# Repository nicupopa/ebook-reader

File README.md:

# OpenBook

## Block Diagram:

## Bill of Materials:

|Component    |Footprint                                    |Link                                                                                                        |
|-------------|---------------------------------------------|------------------------------------------------------------------------------------------------------------|
|BOOT_BUTTON  |BUTTON_CUSYOMV1                              |https://industry.panasonic.com/global/en/products/control/switch/light-touch/number/evqpuj02k               |
|C1           |ESP32_WROVER_EAGLE-LTSPICE_CC0402            |https://eu.mouser.com/ProductDetail/YAGEO/CC0402MRX5R5BB106?qs=zEY9bCHj09eCmUJdZuS5Lg%3D%3D                 |
|C1_BAT       |ESP32_WROVER_EAGLE-LTSPICE_CC0402            |n/a                                                                                                         |
|C1_BAT1      |EAGLE-LTSPICE_CC0402                         |n/a                                                                                                         |
|C1_BAT2      |EAGLE-LTSPICE_CC0402                         |n/a                                                                                                         |
|C2           |ESP32_WROVER_EAGLE-LTSPICE_CC0402            |n/a                                                                                                         |
|C2_BAT\      |ESP32_WROVER_EAGLE-LTSPICE_CC0402            |n/a                                                                                                         |
|C3           |RCL_CPOL-EUCT3528                            |n/a                                                                                                         |
|C4           |ESP32_WROVER_EAGLE-LTSPICE_CC0402            |n/a                                                                                                         |
|C4_USB       |ESP32_WROVER_EAGLE-LTSPICE_CC0402            |n/a                                                                                                         |
|C5           |ESP32_WROVER_EAGLE-LTSPICE_CC0402            |n/a                                                                                                         |
|C5_USB       |ESP32_WROVER_EAGLE-LTSPICE_CC0402            |n/a                                                                                                         |
|C6           |ESP32_WROVER_EAGLE-LTSPICE_CC0402            |n/a                                                                                                         |
|C7           |ESP32_WROVER_EAGLE-LTSPICE_CC0402            |n/a                                                                                                         |
|C8           |ESP32_WROVER_EAGLE-LTSPICE_CC0402            |n/a                                                                                                         |
|C9           |EAGLE-LTSPICE_CC0402                         |n/a                                                                                                         |
|C10          |ESP32_WROVER_EAGLE-LTSPICE_CC0402            |n/a                                                                                                         |
|C10_SUPERCAP |CPH3225A                                     |https://www.snapeda.com/parts/CPH3225A/Seiko+Instruments/view-part/?ref=eda                                 |
|CHANGE_BUTTON|BUTTON_CUSYOMV1                              |https://industry.panasonic.com/global/en/products/control/switch-light-touch/number/evqpuj02k               |
|CHG_LED      |ADAFRUIT_LEDCHIP-LED0603                     |https://www.snapeda.com/parts/KP-1608SURCK/Kingbright/view-part/?ref=search&t=LED%200603                    |
|C_DELAY      |ESP32_WROVER_EAGLE-LTSPICE_CC0402            |n/a                                                                                                         |
|D1           |USBLC6-2SC6Y                                 |https://www.snapeda.com/parts/USBLC6-2SC6Y/STMicroelectronics/view-part/?ref=eda                            |
|D2           |ESP32_WROVER_AVX---SD0805S020S1R0_AVX_...    |https://eu.mouser.com/ProductDetail/KYOCERA-AVX/SD0805S020S1R0?qs=jCA%252BPfw4LHbpkAoSnwrdjw%3D%3D          |
|D3           |MBR0530                                      |https://eu.mouser.com/ProductDetail/KYOCERA-AVX/SD0805S020S1R0?qs=jCA%252BPfw4LHbpkAoSnwrdjw%3D%3D          |
|D4           |MBR0530                                      |https://www.snapeda.com/parts/MBR0530/Onsemi/view-part/?ref=eda                                             |
|D5           |MBR0530                                      |https://www.snapeda.com/parts/MBR0530/Onsemi/view-part/?ref=eda                                             |
|D6           |PGB1010603MR                                 |https://www.snapeda.com/parts/PGB1010603MR/Littelfuse/view-part/?ref=eda                                    |
|D7           |ESP32_WROVER_AVX---SD0805S020S1R0_AVX_...    |https://eu.mouser.com/ProductDetail/KYOCERA-AVX/SD0805S020S1R0?qs=jCA%252BPfw4LHbpkAoSnwrdjw%3D%3D          |
|D8           |PGB1010603MR                                 |https://www.snapeda.com/parts/PGB1010603MR/Littelfuse/view-part/?ref=eda                                    |
|D9           |PGB1010603MR                                 |https://www.snapeda.com/parts/PGB1010603MR/Littelfuse/view-part/?ref=eda                                    |
|D10          |PGB1010603MR                                 |https://www.snapeda.com/parts/PGB1010603MR/Littelfuse/view-part/?ref=eda                                    |
|D11          |PGB1010603MR                                 |https://www.snapeda.com/parts/PGB1010603MR/Littelfuse/view-part/?ref=eda                                    |
|D12          |PGB1010603MR                                 |https://www.snapeda.com/parts/PGB1010603MR/Littelfuse/view-part/?ref=eda                                    |
|EPD_C1       |ESP32_WROVER_EAGLE-LTSPICE_CC0402            |n/a                                                                                                         |
|EPD_C2       |ESP32_WROVER_EAGLE-LTSPICE_CC0402            |n/a                                                                                                         |
|EPD_C5       |ESP32_WROVER_EAGLE-LTSPICE_CC0402            |n/a                                                                                                         |
|EPD_C6       |ESP32_WROVER_EAGLE-LTSPICE_CC0402            |n/a                                                                                                         |
|EPD_C7       |ESP32_WROVER_EAGLE-LTSPICE_CC0402            |n/a                                                                                                         |
|EPD_C8       |ESP32_WROVER_EAGLE-LTSPICE_CC0402            |n/a                                                                                                         |
|EPD_C9       |ESP32_WROVER_EAGLE-LTSPICE_CC0402            |n/a                                                                                                         |
|EPD_C10      |ESP32_WROVER_EAGLE-LTSPICE_CC0402            |n/a                                                                                                         |
|EPD_C11      |ESP32_WROVER_EAGLE-LTSPICE_CC0402            |n/a                                                                                                         |
|EPD_C12      |ESP32_WROVER_EAGLE-LTSPICE_CC0402            |n/a                                                                                                         |
|IC1          |BD5229G-TR                                   |https://componentsearchengine.com/part-view/BD5229G-TR/ROHM%20Semiconductor                                 |
|IC4          |XC6220A331MR-G                               |https://componentsearchengine.com/part-view/XC6220A331MR-G/Torex                                            |
|J1           |FH34SRJ-24S-0.5SH_99_                        |https://componentsearchengine.com/part-view/XC6220A331MR-G/Torex                                            |
|J2           |SAMACSYS_PARTS_USB4110-GF-A                  |https://componentsearchengine.com/part-view/USB4110-GF-A/GCT%20(GLOBAL%20CONNECTOR%20TECHNOLOGY             |
|J3           |QWIIC_CONNECTORJS-1MM                        |n/a                                                                                                         |
|J4           |112A-TAAR-R03_ATTEND                         |https://store.comet.srl.ro/Catalogue/Product/43497/                                                         |
|L1           |744043680IND_4828-WE-TPC_WRE                 |https://eu.mouser.com/ProductDetail/Wurth-Elektronik/744043680?qs=PGXP4M47uW6VkZq%252BkzjrHA%3D%3D          |
|PFMF.050.1   |ESP32C6_VARISTORCN1812                       |https://www.mouser.co.uk/ProductDetail/EPCOS-TDK/B72520T0350K062?qs=dEfas%2FXlABIszF52uu7vrg%3D%3D          |
|Q1           |ESP32_WROVER_SPARKFUN-DISCRETESEMI_MOSFET_...|https://componentsearchengine.com/part-view/DMG2305UX-7/Diodes%20Incorporated                               |
|Q2           |ESP32_WROVER_SPARKFUN-DISCRETESEMI_MOSFET_...|n/a                                                                                                         |
|Q3           |D8                                           |https://componentsearchengine.com/part-view/SI1308EDL-T1-GE3/Vishay                                         |
|R1           |ESP32_WROVER_EAGLE-LTSPICE_RR0402            |n/a                                                                                                         |
|R1-PINH      |ESP32_WROVER_EAGLE-LTSPICE_RR0402            |n/a                                                                                                         |
|R1-PINH1     |ESP32_WROVER_EAGLE-LTSPICE_RR0402            |n/a                                                                                                         |
|R1_BAT       |ESP32_WROVER_EAGLE-LTSPICE_RR0402            |n/a                                                                                                         |
|R1_PWRUSB    |ESP32_WROVER_EAGLE-LTSPICE_RR0402            |n/a                                                                                                         |
|R2           |ESP32_WROVER_EAGLE-LTSPICE_RR0402            |https://componentsearchengine.com/part-view/R0402%201%25%20100%20K%20(RC0402FR-07100KL                      |
|R2-PINH      |ESP32_WROVER_EAGLE-LTSPICE_RR0402            |n/a                                                                                                         |
|R2-PINH1     |ESP32_WROVER_EAGLE-LTSPICE_RR0402            |n/a                                                                                                         |
|R2-USB       |ESP32_WROVER_EAGLE-LTSPICE_RR0402            |n/a                                                                                                         |
|R2-USB1      |ESP32_WROVER_EAGLE-LTSPICE_RR0402            |n/a                                                                                                         |
|R2_BAT       |ESP32_WROVER_EAGLE-LTSPICE_RR0402            |n/a                                                                                                         |
|R3           |ESP32_WROVER_EAGLE-LTSPICE_RR0402            |n/a                                                                                                         |
|R4           |ESP32_WROVER_EAGLE-LTSPICE_RR0402            |n/a                                                                                                         |
|R5           |ESP32_WROVER_EAGLE-LTSPICE_RR0402            |n/a                                                                                                         |
|R6           |ESP32_WROVER_EAGLE-LTSPICE_RR0402            |n/a                                                                                                         |
|R7           |ESP32_WROVER_EAGLE-LTSPICE_RR0402            |n/a                                                                                                         |
|R8           |ESP32_WROVER_EAGLE-LTSPICE_RR0402            |n/a                                                                                                         |
|R9           |ESP32_WROVER_EAGLE-LTSPICE_RR0402            |n/a                                                                                                         |
|R10          |ESP32_WROVER_EAGLE-LTSPICE_RR0402            |n/a                                                                                                         |
|RESET_BUTTON |BUTTON_CUSYOMV1                              |https://industry.panasonic.com/global/en/products/control/switch/light-touch/number/evqpuj02k               |
|R_BOOT       |ESP32_WROVER_EAGLE-LTSPICE_RR0402            |n/a                                                                                                         |
|R_CAPACITOR  |ESP32_WROVER_EAGLE-LTSPICE_RR0402            |n/a                                                                                                         |
|R_CHANGE     |ESP32_WROVER_EAGLE-LTSPICE_RR0402            |n/a                                                                                                         |
|R_CL1        |ESP32_WROVER_EAGLE-LTSPICE_RR0402            |n/a                                                                                                         |
|R_RESET      |ESP32_WROVER_EAGLE-LTSPICE_RR0402            |n/a                                                                                                         |
|SENSOR2      |ESP32_WROVER_BME680_BME680                   |https://www.snapeda.com/parts/BME680/Bosch/view-part/?welcome=home                                          |
|SJ1          |SJ                                           |https://grabcad.com/library/solder-jumpers-1                                                                |
|U1           |W25Q512JVEIQ                                 |https://www.snapeda.com/parts/W25Q512JVEIQ/Winbond+Electronics/view-part/?ref=eda                           |
|U2           |ESP32-C6-WROOM-1-N8                          |https://www.snapeda.com/parts/ESP32-C6-WROOM-1-N8/Espressif+Systems/view-part/?ref=eda                      |
|U3           |DS3231SN#                                    |https://www.snapeda.com/parts/DS3231SN%23/Analog+Devices/view-part/?ref=eda                                 |
|U4           |MAX17048G+T10                                |https://www.snapeda.com/parts/MAX17048G+T10/Analog+Devices/view-part/?ref=eda                               |
|U5           |ESP32_WROVER_SPARKFUN-IC-POWER_MCP73831      |https://eu.mouser.com/ProductDetail/Microchip-Technology/MCP73831T-2ACI-OT?qs=yUQqVecv4qvbBQBGbHx0Mw%3D%3Dcf|

## Detailed Hardware Description/Specs:

### Microcontroller – ESP32-C6-WROOM-1-N8

- **Processor:** 32-bit RISC-V, up to 160 MHz  
- **Memory:** 512 KB internal SRAM, 8 MB external flash (W25Q512JVEIQ)  
- **Connectivity:** Wi-Fi 6 (802.11ax), Bluetooth 5 (LE), IEEE 802.15.4 (Thread/Zigbee), USB 2.0 (Full-Speed)  
- **Peripherals:** SPI, I²C, UART, PWM, ADC, multiple GPIOs  

### External Memory – W25Q512JVEIQ

- **Capacity:** 512 Mbit (64 MB)  
- **Interface:** Quad SPI (QPI)  
- **Operating Frequency:** Up to 133 MHz  
- **Supply Voltage:** 2.7 V to 3.6 V  
- **Features:** high endurance (100k write/erase cycles)

### Real-Time Clock – DS3231SN#

- **Accuracy:** ±2 ppm from 0°C to +40°C  
- **Interface:** I²C  
- **Features:** Integrated temperature-compensated crystal oscillator (TCXO)  
- **Voltage Range:** 2.3 V to 5.5 V  
- **Additional:** Battery backup support, 2 programmable alarms, 1Hz square wave output

### Battery Monitor – MAX17048G+T10

- **Function:** Fuel gauge for single-cell Li-ion/Li-Po batteries
- **Interface:** I²C  
- **Voltage Range:** 2.5 V to 4.5 V  
- **Power Consumption:** Ultra-low quiescent current (~23 µA)

### Charge Controller – MCP73831

- **Battery Type:** Single-cell Li-ion/Li-Po  
- **Charging Current:** Programmable up to 500 mA  
- **Interface:** Standalone (no I²C/SPI)  
- **Input Voltage:** 3.75 V to 6 V  
- **Status Output:** Charge status indication via LED

### Environmental Sensor – BME688

- **Measurements:** Temperature, humidity, pressure, gas (VOC, air quality)  
- **Interface:** I²C, SPI  
- **Temperature Range:** -40 °C to +85 °C  
- **Gas Sensor:** AI-based VOC and gas mixture detection  
- **Power Consumption:** Ultra-low power (ideal for mobile/wearables)

### E-Paper Display

- **Interface:** SPI  
- **Resolution:** 800×480
- **Power Usage:** Extremely low (only consumes power during refresh)  
- **Features:** Excellent sunlight readability, wide viewing angles

### Qwiic Connector

- **Type:** JST SH 1.0 mm 4-pin connector  
- **Purpose:** Standardized I²C interconnect for sensors/modules  
- **Voltage:** 3.3 V logic  
- **Pins:** SDA, SCL, VCC, GND  

### SD Memory Card Connector – 112A-TAAR-R03

- **Type:** MicroSD card socket
- **Interface:** SPI or SDIO  
- **Voltage:** Typically 3.3 V logic  
- **Features:** Push-push eject mechanism, card detect switch  
- **Use Case:** Data logging, file storage, media playback

## ESP32-C6 Pin Usage:

| Device        | ESP32-C6 Pin   | Connected Component        | Function                                    |
|:--------------|:---------------|:---------------------------|:--------------------------------------------|
| U2 - ESP32-C6 | GPIO0          | BOOT button                | Enables bootloader mode on startup (input)  |
| U2 - ESP32-C6 | GPIO1          | UART TX                    | Serial communication for debugging/flashing |
| U2 - ESP32-C6 | GPIO2          | UART RX                    | Serial communication for debugging/flashing |
| U2 - ESP32-C6 | GPIO3          | BME688 (I²C SDA)           | Environmental sensor data line              |
| U2 - ESP32-C6 | GPIO4          | BME688 (I²C SCL)           | Environmental sensor clock line             |
| U2 - ESP32-C6 | GPIO5          | MAX17048 (I²C SDA)         | Battery monitor data line (shared bus)      |
| U2 - ESP32-C6 | GPIO6          | MAX17048 (I²C SCL)         | Battery monitor clock line (shared bus)     |
| U2 - ESP32-C6 | GPIO7          | Qwiic Connector SDA        | I²C communication (shared with sensors)     |
| U2 - ESP32-C6 | GPIO8          | Qwiic Connector SCL        | I²C communication (shared with sensors)     |
| U2 - ESP32-C6 | GPIO9          | DS3231 RTC SDA             | I²C data line for real-time clock           |
| U2 - ESP32-C6 | GPIO10         | DS3231 RTC SCL             | I²C clock line for real-time clock          |
| U2 - ESP32-C6 | GPIO18         | E-Paper Display (SPI MOSI) | Serial data out to display                  |
| U2 - ESP32-C6 | GPIO19         | E-Paper Display (SPI CLK)  | Serial clock for display communication      |
| U2 - ESP32-C6 | GPIO20         | E-Paper Display (CS)       | Chip select line                            |
| U2 - ESP32-C6 | GPIO21         | E-Paper Display (DC)       | Data/Command control pin                    |
| U2 - ESP32-C6 | GPIO22         | E-Paper Display (RST)      | Reset line for display                      |
| U2 - ESP32-C6 | GPIO23         | E-Paper Display (BUSY)     | Busy status signal input                    |
| U2 - ESP32-C6 | GPIO13         | SD Card (SPI CS)           | Chip select line for SD card                |
| U2 - ESP32-C6 | GPIO14         | SD Card (SPI MISO)         | Master In Slave Out - reads from SD         |
| U2 - ESP32-C6 | GPIO15         | SD Card (SPI MOSI)         | Master Out Slave In - writes to SD          |
| U2 - ESP32-C6 | GPIO16         | SD Card (SPI CLK)          | SPI clock for SD card communication         |

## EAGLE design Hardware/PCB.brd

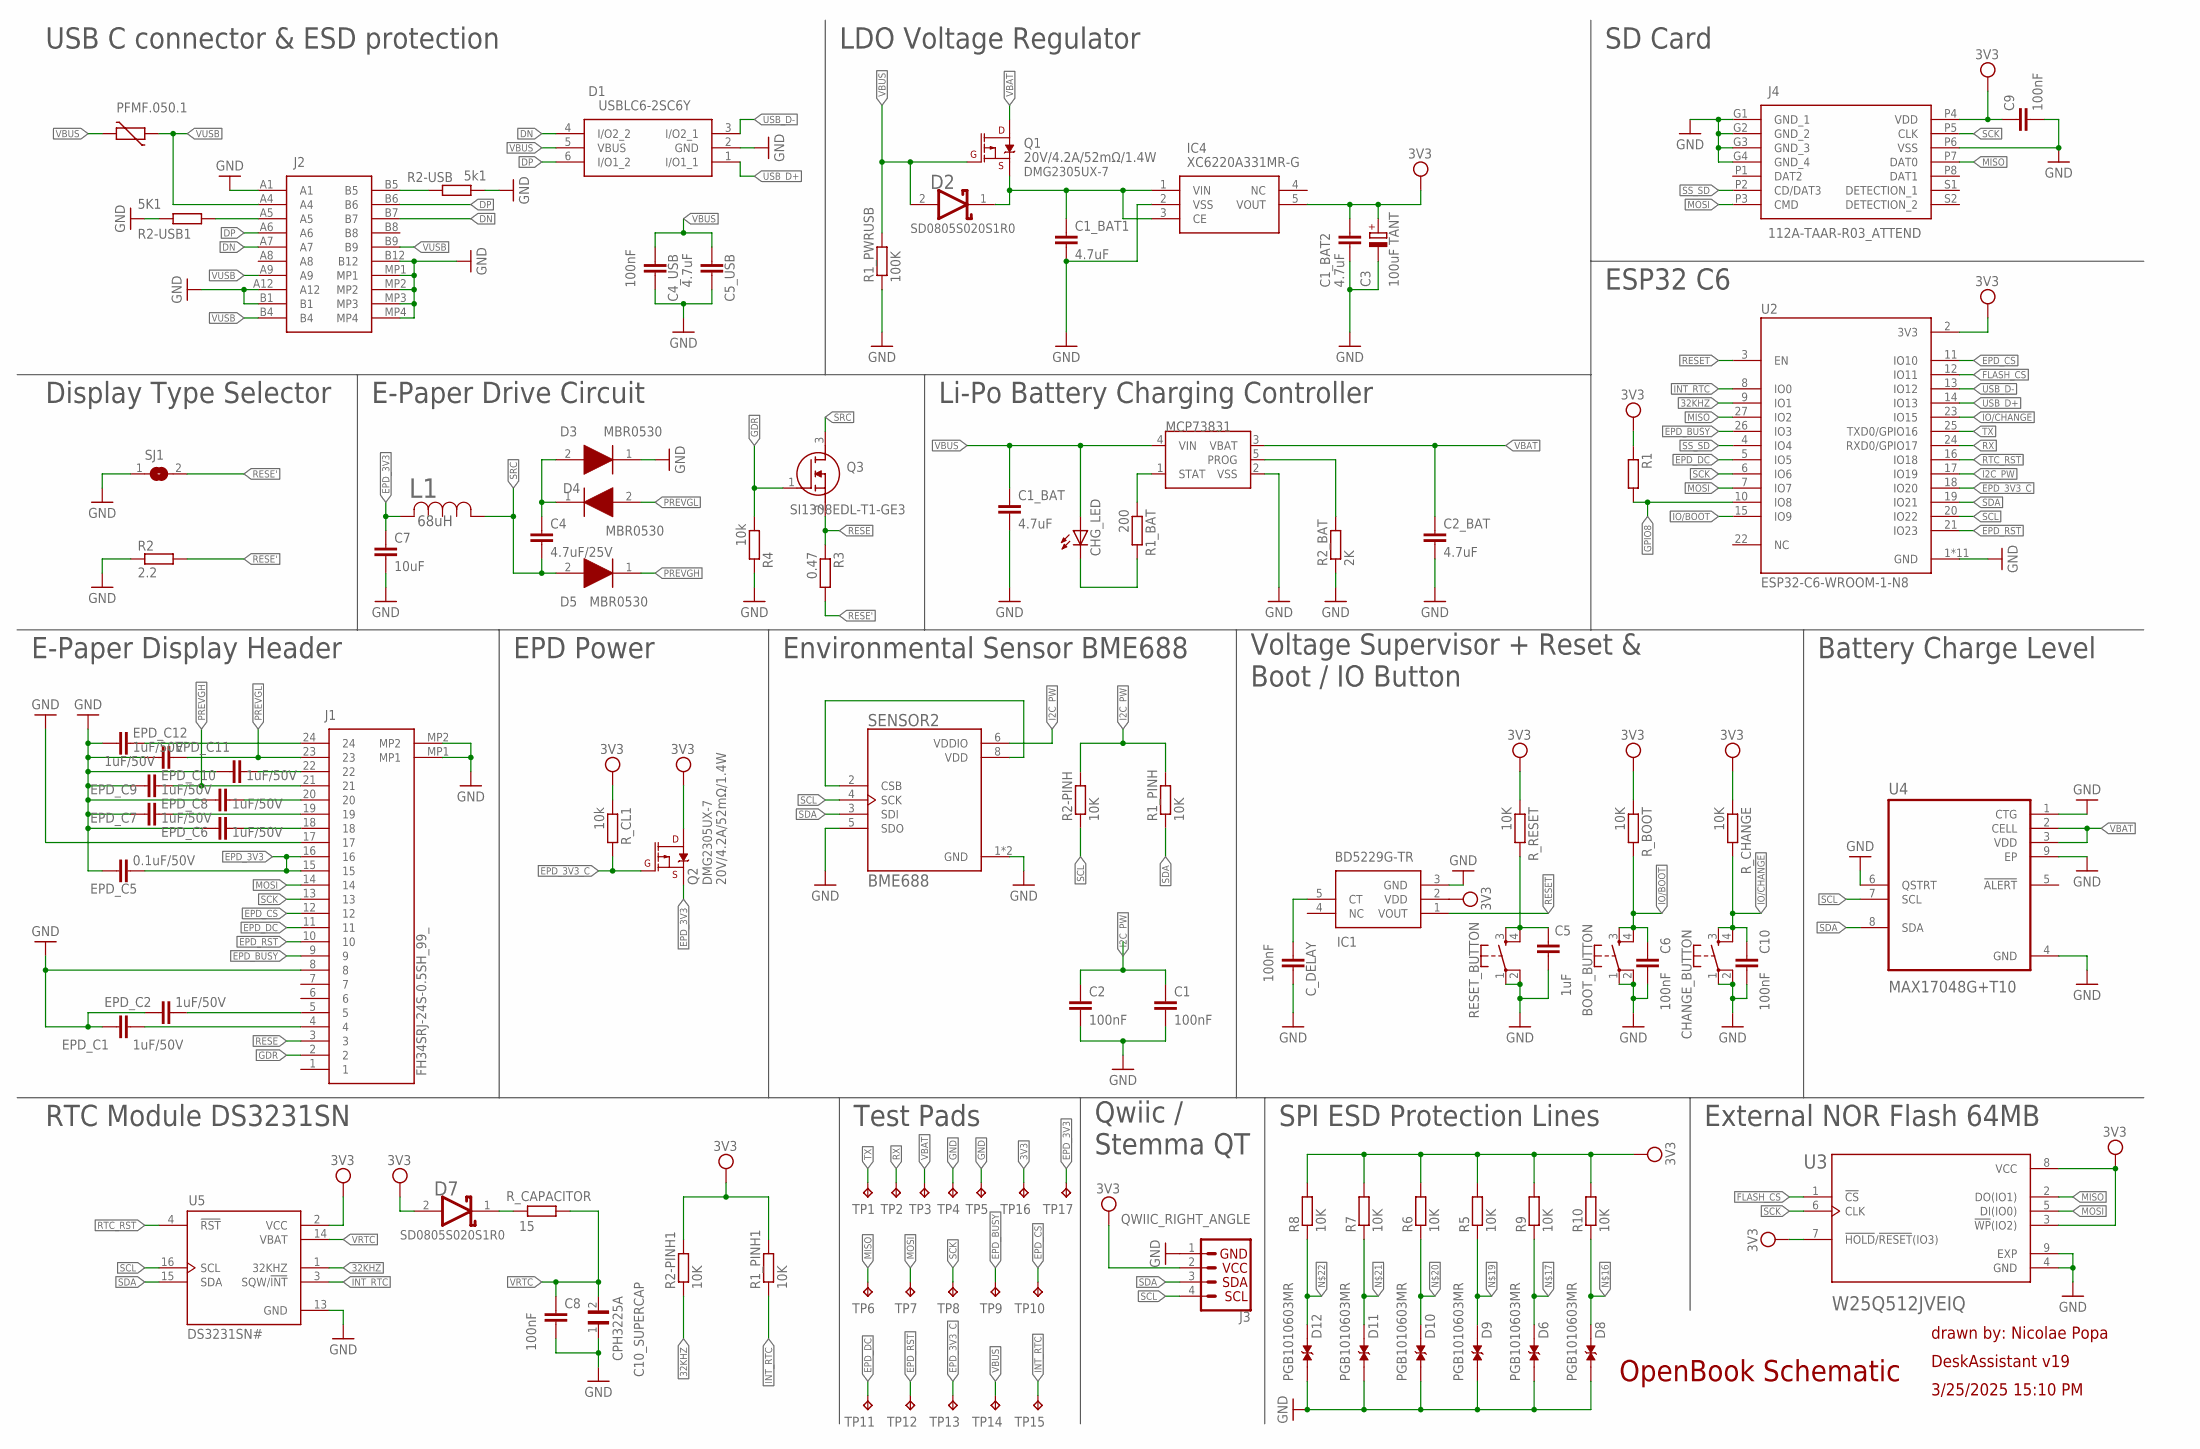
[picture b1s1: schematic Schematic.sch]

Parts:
BOOT_BUTTON: BUTTON_CUSYOMV1; MYBUTTON
C1, C2, C4_USB, C6, C8, C10: 100nF; EAGLE-LTSPICE_C0402
C1_BAT, C1_BAT1, C1_BAT2, C2_BAT, C5_USB: 4.7uF; EAGLE-LTSPICE_C0402
C3: 100uF TANT; RCL_CT3528
C4: 4.7uF/25V; EAGLE-LTSPICE_C0402
C5: 1uF; EAGLE-LTSPICE_C0402
C7: 10uF; EAGLE-LTSPICE_C0402
C9: 100nF; ESP32_WROVER_EAGLE-LTSPICE_C0402
C10_SUPERCAP: CPH3225A; CAPCP3225X100N
CHANGE_BUTTON: BUTTON_CUSYOMV1; MYBUTTON
CHG_LED: ADAFRUIT_LEDCHIP-LED0603; ADAFRUIT_CHIP-LED0603
C_DELAY: 100nF; EAGLE-LTSPICE_C0402
D1: USBLC6-2SC6Y; SOT95P280X145-6N
D2: ESP32_WROVER_AVX---SD0805S020S1R0_AVX_SD0805S020S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; ESP32_WROVER_AVX---SD0805S020S1R0_AVX_SD0805S020S1R0_0
D3, D4, D5: MBR0530; SOD3716X135N
D6, D8, D9, D10, D11, D12: PGB1010603MR; DIOC1608X36N
D7: SD0805S020S1R0; ESP32_WROVER_AVX---SD0805S020S1R0_AVX_SD0805S020S1R0_0
EPD_C1, EPD_C2, EPD_C6, EPD_C7, EPD_C8, EPD_C9, EPD_C10, EPD_C11, EPD_C12: 1uF/50V; EAGLE-LTSPICE_C0402
EPD_C5: 0.1uF/50V; EAGLE-LTSPICE_C0402
IC1: BD5229G-TR; SOT95P280X125-5N
IC4: XC6220A331MR-G; SOT95P280X120-5N
J1: FH34SRJ-24S-0.5SH_99_; FH34SRJ24S05SH99
J2: SAMACSYS_PARTS_USB4110-GF-A; SAMACSYS_PARTS_USB4110GFA
J3: QWIIC_RIGHT_ANGLE; JST04_1MM_RA
J4: 112A-TAAR-R03_ATTEND; 112ATAARR03ATTEND
L1: 68uH; IND_4828-WE-TPC_WRE
PFMF.050.1: ESP32C6_VARISTORCN1812; ESP32C6_VARISTOR_CT/CN1812
Q1, Q2: 20V/4.2A/52mΩ/1.4W; ESP32_WROVER_SPARKFUN-DISCRETESEMI_SOT23-3
Q3: SI1308EDL-T1-GE3; SOT65P210X110-3N
R1: ESP32_WROVER_EAGLE-LTSPICE_RR0402; ESP32_WROVER_EAGLE-LTSPICE_R0402
R1_BAT: 200; ESP32_WROVER_EAGLE-LTSPICE_R0402
R1_PINH, R1_PINH1, R2-PINH, R2-PINH1, R5, R6, R7, R8, R9, R10: 10K; ESP32_WROVER_EAGLE-LTSPICE_R0402
R1_PWRUSB: 100K; ESP32_WROVER_EAGLE-LTSPICE_R0402
R2: 2.2; ESP32_WROVER_EAGLE-LTSPICE_R0402
R2-USB: 5k1; ESP32_WROVER_EAGLE-LTSPICE_R0402
R2-USB1: 5K1; ESP32_WROVER_EAGLE-LTSPICE_R0402
R2_BAT: 2K; ESP32_WROVER_EAGLE-LTSPICE_R0402
R3: 0.47; ESP32_WROVER_EAGLE-LTSPICE_R0402
R4: 10k; ESP32_WROVER_EAGLE-LTSPICE_R0402
RESET_BUTTON: BUTTON_CUSYOMV1; MYBUTTON
R_BOOT: 10K; ESP32_WROVER_EAGLE-LTSPICE_R0402
R_CAPACITOR: 15; ESP32_WROVER_EAGLE-LTSPICE_R0402
R_CHANGE: 10K; ESP32_WROVER_EAGLE-LTSPICE_R0402
R_CL1: 10k; ESP32_WROVER_EAGLE-LTSPICE_R0402
R_RESET: 10K; ESP32_WROVER_EAGLE-LTSPICE_R0402
SENSOR2: BME688; ESP32_WROVER_BME680_PSON80P300X300X100-8N
SJ1: SJ
TP1, TP2, TP3, TP4, TP5, TP6, TP7, TP8, TP9, TP10, TP11, TP12, TP13, TP14, TP15, TP16, TP17: TPTP20R; TP20R
U1: MCP73831; ESP32_WROVER_SPARKFUN-IC-POWER_SOT23-5
U2: ESP32-C6-WROOM-1-N8; XCVR_ESP32-C6-WROOM-1-N8
U3: W25Q512JVEIQ; SON127P600X800X80-9N
U4: MAX17048G+T10; SON50P200X200X80-9N
U5: DS3231SN#; SOIC127P1032X265-16N

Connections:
3V3: C1_BAT2.1, C3.+, C9.1, D7.2 (ANODE), IC1.2 (VDD), IC4.5 (VOUT), J3.2, J4.P4 (VDD), Q2.3 (D), R1.1, R1_PINH1.2, R2-PINH1.2, R5.2, R6.2, R7.2, R8.2, R9.2, R10.2, R_BOOT.1, R_CHANGE.1, R_CL1.1, R_RESET.1, TP16.TP, U2.2 (3V3), U3.3 (!WP!(IO2)), U3.7 (!HOLD!/!RESET!(IO3)), U3.8 (VCC), U5.2 (VCC)
32KHZ: R2-PINH1.1, U2.9 (IO1), U5.1 (32KHZ)
DN: D1.4 (I/O2_2), J2.A7, J2.B7
DP: D1.6 (I/O1_2), J2.A6, J2.B6
EPD_3V3: C7.1, EPD_C5.1, J1.15, J1.16, L1.2, Q2.2 (S), TP17.TP
EPD_3V3_C: Q2.1 (G), R_CL1.2, TP13.TP, U2.18 (IO20)
EPD_BUSY: J1.9, TP9.TP, U2.26 (IO3)
EPD_CS: J1.12, TP10.TP, U2.11 (IO10)
EPD_DC: J1.11, TP11.TP, U2.5 (IO5)
EPD_RST: J1.10, TP12.TP, U2.21 (IO23)
FLASH_CS: U2.12 (IO11), U3.1 (!CS)
GDR: J1.2, Q3.1 (G), R4.1
GND: BOOT_BUTTON.1, BOOT_BUTTON.2, C1.2, C1_BAT.2, C1_BAT1.2, C1_BAT2.2, C2.2, C2_BAT.2, C3.-, C4_USB.2, C5.2, C5_USB.2, C6.2, C7.2, C8.2, C9.2, C10.2, C10_SUPERCAP.1, CHANGE_BUTTON.1, CHANGE_BUTTON.2, C_DELAY.2, D1.2 (GND), D3.1 (K), D6.1, D8.1, D9.1, D10.1, D11.1, D12.1, EPD_C1.2, EPD_C2.2, EPD_C5.2, EPD_C6.2, EPD_C7.2, EPD_C8.2, EPD_C9.2, EPD_C10.2, EPD_C11.2, EPD_C12.2, IC1.3 (GND), IC4.2 (VSS), J1.8, J1.17, J1.MP1, J1.MP2, J2.A1, J2.A12, J2.B1, J2.B12, J2.MP1, J2.MP2, J2.MP3, J2.MP4, J3.1, J4.G1 (GND_1), J4.G2 (GND_2), J4.G3 (GND_3), J4.G4 (GND_4), J4.P6 (VSS), R1_PWRUSB.1, R2.1, R2-USB.2, R2-USB1.1, R2_BAT.1, R4.2, RESET_BUTTON.1, RESET_BUTTON.2, SENSOR2.1 (GND), SENSOR2.5 (SDO), SENSOR2.7 (GND), SJ1.1, TP4.TP, TP5.TP, U1.2 (VSS), U2.1 (GND), U2.28 (GND), U2.29_1 (GND), U2.29_2 (GND), U2.29_3 (GND), U2.29_4 (GND), U2.29_5 (GND), U2.29_6 (GND), U2.29_7 (GND), U2.29_8 (GND), U2.29_9 (GND), U3.4 (GND), U3.9 (EXP), U4.1 (CTG), U4.4 (GND), U4.6 (QSTRT), U4.9 (EP), U5.13 (GND)
GPIO8: R1.2, U2.10 (IO8)
I2C_PW: C1.1, C2.1, R1_PINH.2, R2-PINH.2, SENSOR2.6 (VDDIO), U2.17 (IO19)
INT_RTC: R1_PINH1.1, TP15.TP, U2.8 (IO0), U5.3 (SQW/!INT)
IO/BOOT: BOOT_BUTTON.3, BOOT_BUTTON.4, C6.1, R_BOOT.2, U2.15 (IO9)
IO/CHANGE: C10.1, CHANGE_BUTTON.3, CHANGE_BUTTON.4, R_CHANGE.2, U2.23 (IO15)
MISO: J4.P7 (DAT0), TP6.TP, U2.27 (IO2), U3.2 (DO(IO1))
MOSI: J1.14, J4.P3 (CMD), TP7.TP, U2.7 (IO7), U3.5 (DI(IO0))
unnamed: J2.A5, R2-USB1.2
unnamed: C1_BAT1.1, D2.1 (CATHODE), IC4.1 (VIN), IC4.3 (CE), Q1.2 (S)
unnamed: R1_BAT.1, U1.1 (STAT)
unnamed: C4.1, D3.2 (A), D4.1 (K)
unnamed: CHG_LED.C, R1_BAT.2
unnamed: EPD_C12.1, J1.24
unnamed: R2_BAT.2, U1.5 (PROG)
unnamed: SENSOR2.2 (CSB), SENSOR2.8 (VDD)
unnamed: C_DELAY.1, IC1.5 (CT)
unnamed: EPD_C10.1, J1.22
unnamed: EPD_C8.1, J1.20
unnamed: EPD_C7.1, J1.19
unnamed: J2.B5, R2-USB.1
unnamed: EPD_C6.1, J1.18
unnamed: D8.2, R10.1
unnamed: D6.2, R9.1
unnamed: C5.1, RESET_BUTTON.3, RESET_BUTTON.4, R_RESET.2
unnamed: D9.2, R5.1
unnamed: D10.2, R6.1
unnamed: D11.2, R7.1
unnamed: D12.2, R8.1
unnamed: EPD_C2.1, J1.5
unnamed: EPD_C1.1, J1.4
unnamed: D7.1 (CATHODE), R_CAPACITOR.2
PREVGH: D5.1 (K), EPD_C9.1, J1.21
PREVGL: D4.2 (A), EPD_C11.1, J1.23
RESE: J1.3, Q3.2 (S), R3.1
RESE': R2.2, R3.2, SJ1.2
RESET: IC1.1 (VOUT), U2.3 (EN)
RTC_RST: U2.16 (IO18), U5.4 (!RST)
RX: TP2.TP, U2.24 (RXD0/GPIO17)
SCK: J1.13, J4.P5 (CLK), TP8.TP, U2.6 (IO6), U3.6 (CLK)
SCL: J3.4, R2-PINH.1, SENSOR2.4 (SCK), U2.20 (IO22), U4.7 (SCL), U5.16 (SCL)
SDA: J3.3, R1_PINH.1, SENSOR2.3 (SDI), U2.19 (IO21), U4.8 (SDA), U5.15 (SDA)
SRC: C4.2, D5.2 (A), L1.1, Q3.3 (D)
SS_SD: J4.P2 (CD/DAT3), U2.4 (IO4)
TX: TP1.TP, U2.25 (TXD0/GPIO16)
USB_D+: D1.1 (I/O1_1), U2.14 (IO13)
USB_D-: D1.3 (I/O2_1), U2.13 (IO12)
VBAT: C2_BAT.1, Q1.3 (D), TP3.TP, U1.3 (VBAT), U4.2 (CELL), U4.3 (VDD)
VBUS: C1_BAT.1, C4_USB.1, C5_USB.1, CHG_LED.A, D1.5 (VBUS), D2.2 (ANODE), PFMF.050.1.2, Q1.1 (G), R1_PWRUSB.2, TP14.TP, U1.4 (VIN)
VRTC: C8.1, C10_SUPERCAP.2, R_CAPACITOR.1, U5.14 (VBAT)
VUSB: J2.A4, J2.A9, J2.B4, J2.B9, PFMF.050.1.1

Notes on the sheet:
USB C connector & ESD protection
Display Type Selector
E-Paper Drive Circuit
LDO Voltage Regulator
SD Card
Li-Po Battery Charging Controller
ESP32 C6
E-Paper Display Header
EPD Power
Environmental Sensor BME688
Voltage Supervisor + Reset & Boot / IO Button
Battery Charge Level
RTC Module DS3231SN
Test Pads
Qwiic / Stemma QT
External NOR Flash 64MB
SPI ESD Protection Lines
OpenBook Schematic
drawn by: Nicolae Popa
DeskAssistant v19
3/25/2025 15:10 PM

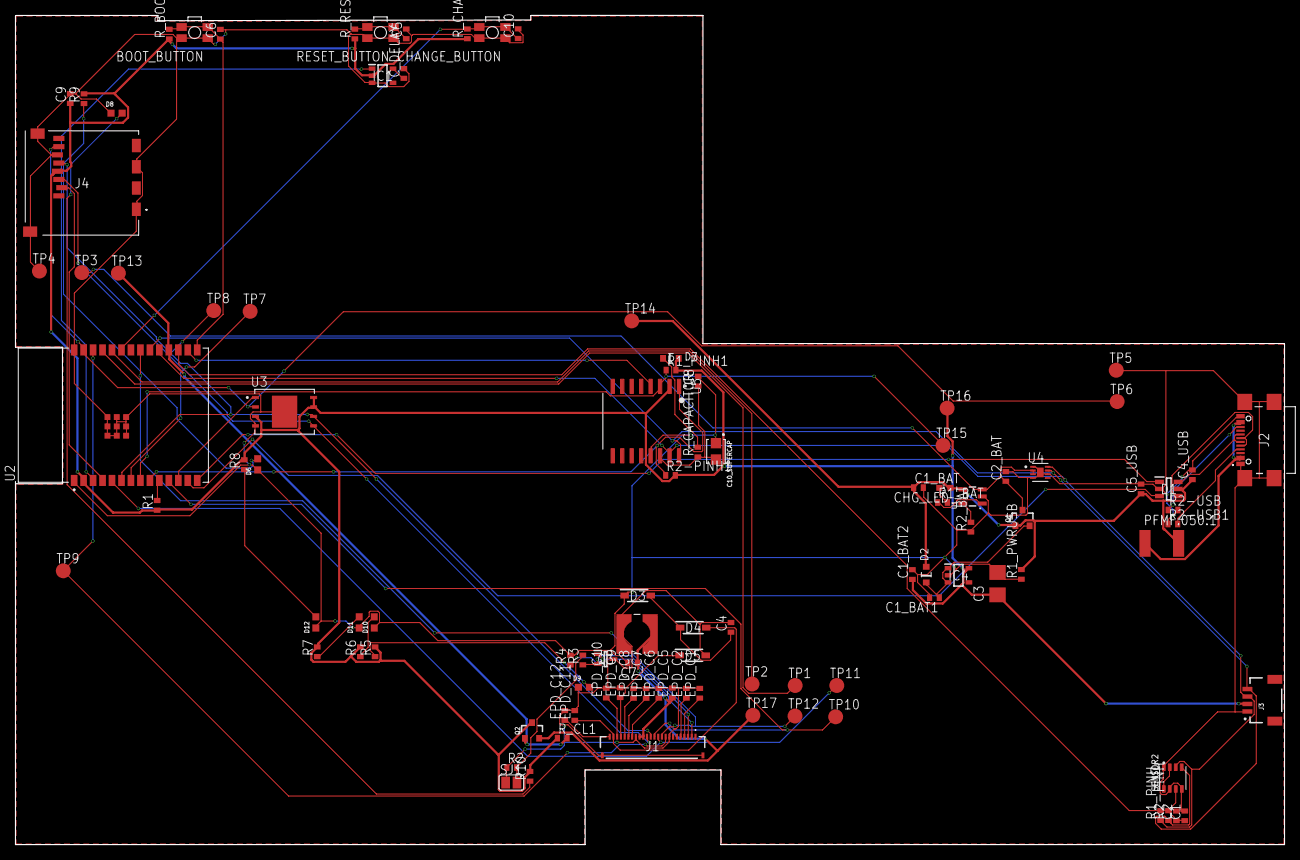
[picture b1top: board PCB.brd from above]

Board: 2 copper layers, 170.2 x 111.2 mm, 103 parts (0 on the bottom side), 63 nets.

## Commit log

2025-03-29 Add schematic implementation
2025-03-29 Add Schematic.sch
2025-04-04 Add PCB
2025-04-05 Update Schematic and PCB
2025-04-06 Update PCB and Schematic
2025-04-06 Add Complete Design
2025-04-06 Update PCB
2025-04-06 Add manufacturing files
2025-04-06 Create LICENSE
2025-04-06 Add media
2025-04-06 Remove old files
2025-04-06 Add misc.
2025-04-06 Add minor tweaks
2025-04-06 Add exploded version
2025-04-06 Update exploded view
2025-04-12 Solve schematic issue
2025-04-12 Fix PCB issues
2025-04-12 Fix enclosure and battery
2025-04-12 Add extra media

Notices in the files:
parts and their libraries:
COPYRIGHT: Copyright (C) 2024 Ultra Librarian. All rights reserved.
